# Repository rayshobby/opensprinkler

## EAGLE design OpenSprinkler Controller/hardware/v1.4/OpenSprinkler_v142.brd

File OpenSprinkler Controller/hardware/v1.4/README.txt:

OpenSprinkler v1.42 (minor update)
Changes from v1.4

- Added one 5.6V zener diode and removed the PTC fuse.
- Changed capacitor CT to 100pF in order to reduce switching regulator noise.
- Combined four 10K resistors from 1.4u to one 10Kx4resistor network.
- Switching positions of rain sensor terminal and zone expansion connector. Expansion connector now uses 2×4 right-angle male header.

=================================

OpenSprinkler v1.4 (minor update)
Changes from v1.3:

- Added DS1307 real-time clock (RTC) and button cell battery (CR1220). Removed 24LC128 external EEPROM due to PCB space constraint.
- Changed a couple of pin connections for the shift register and LCD. D3 is now used for rain sensor (can be used for other purpose if not using a rain sensor). Analog pins A2 and A3 are free; also, if not using RFM12B transceiver, digital pins D2 and D10 are free.
- Added SMT (surface mount) version 1.4s. The SMT version has two additional analog pins A6 and A7 due to the surface mount version of ATmega328. The RJ45 Ethernet jack is changed to use HanRun H911105A.

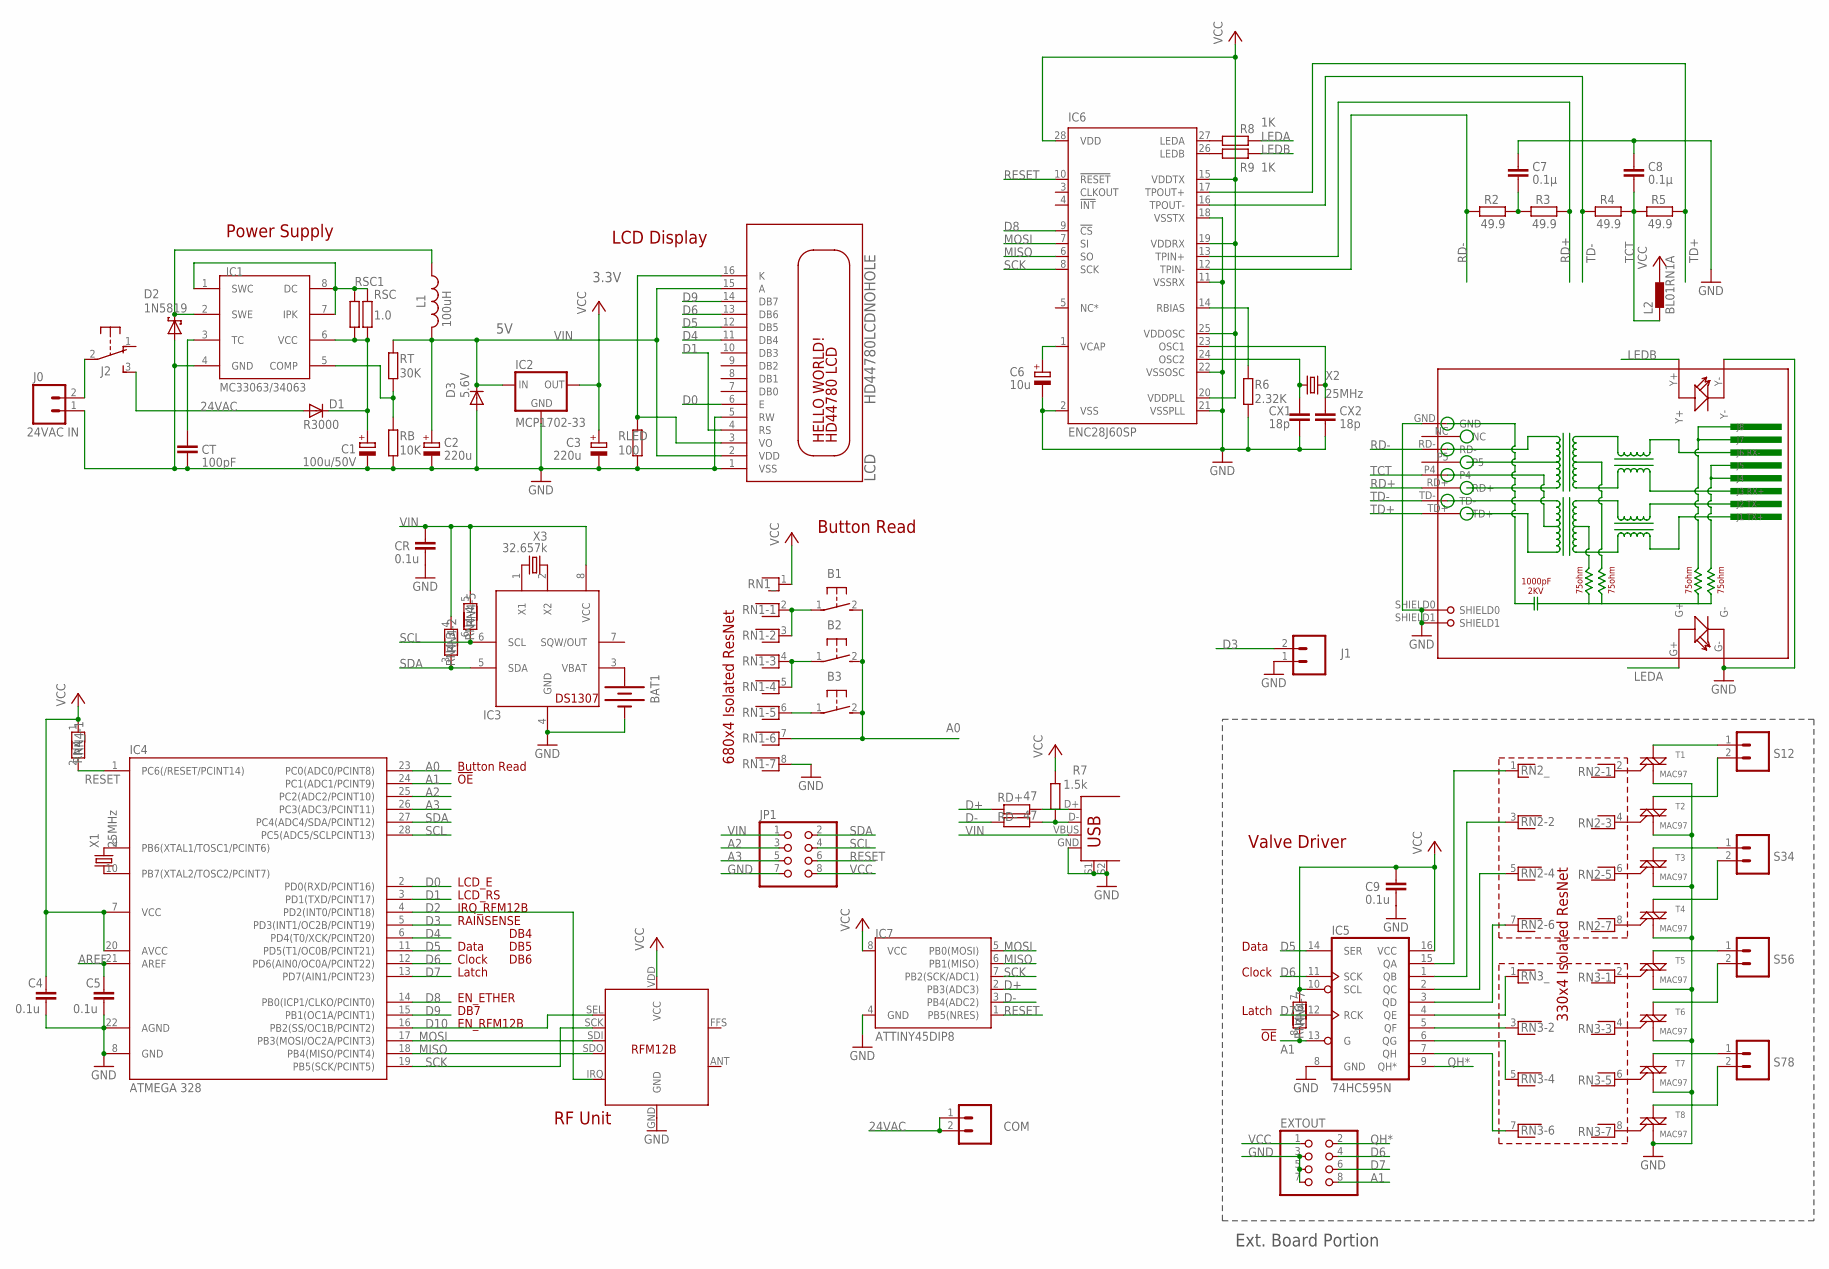
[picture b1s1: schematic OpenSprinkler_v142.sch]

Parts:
B1, B2, B3: 31-XX; B3F-31XX
BAT1: BATTERY12PTH; BATTCON_12MM_PTH
C1: 100u/50V; E3,5-8
C2, C3: 220u; E2-5
C4, C5, C9: 0.1u; C025-024X044
C6: 10u; E1,8-4
C7, C8: 0.1µ; C025-024X044
COM: M025MM; SCREWTERMINAL-5MM-2
CR: 0.1u; C025-024X044
CT: 100pF; C025-024X044
CX1, CX2: 18p; C025-024X044
D1: R3000; DO41-7.6
D2: 1N5819; DO41-7.6
D3: 5.6V; DO35-7
EXTOUT: PINHD-2X4; 2X04
IC1: MC33063/MC34063P; DIL08
IC2: MCP1702-33; TO92-INLINE
IC3: DS1307; DIL08
IC4: ATMEGA 328; DIL28-3
IC5: 74HC595N; DIL16
IC6: ENC28J60SP; DIL28-3
IC7: ATTINY45DIP8; DIP08
IC8: RFM12B
J0: 24VAC IN; SCREWTERMINAL-5MM-2
J1: M025MM; SCREWTERMINAL-5MM-2
J2: EG1206
JP1: PINHD-2X4; 2X04
L1: 100uH; 6000-XXXX-RC
L2: BL01RN1A
LCD: HD44780LCDNOHOLE; LCD1602A
R2, R3, R4, R5: 49.9; 0204/7
R6: 2.32K; 0204/7
R7: 1.5k; 0204/7
R8, R9: 1K; 0204/7
RB: 10K; 0204/7
RD+: 47; 0204/7
RD-: 47; 0204/7
RJ1: HR911105A
RLED: 100; 0204/7
RN1, RN2, RN3, RN4: RNX7; RN-8
RSC, RSC1: 1.0; 0204/7
RT: 30K; 0204/7
S12, S34, S56, S78: M025MM; SCREWTERMINAL-5MM-2
T1, T2, T3, T4, T5, T6, T7, T8: MAC97; TO-92
USB: USB+SHIELD; USB-B-PTH
X1, X2: 25MHz; HC49US
X3: 32.657k; TC26H

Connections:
24VAC: COM.1, COM.2, D1.A, J2.3 (S)
A0: B1.2 (S), B2.2 (S), B3.2 (S), IC4.23 (PC0(ADC0/PCINT8)), RN1.7
A1: EXTOUT.8, IC4.24 (PC1(ADC1/PCINT9)), IC5.13 (G), RN4.8
A2: IC4.25 (PC2(ADC2/PCINT10)), JP1.3
A3: IC4.26 (PC3(ADC3/PCINT11)), JP1.5
AREF: C5.1, IC4.21 (AREF)
D0: IC4.2 (PD0(RXD/PCINT16)), LCD.6 (E)
D1: IC4.3 (PD1(TXD/PCINT17)), LCD.4 (RS)
D2: IC4.4 (PD2(INT0/PCINT18)), IC8.IRQ
D3: IC4.5 (PD3(INT1/OC2B/PCINT19)), J1.2
D4: IC4.6 (PD4(T0/XCK/PCINT20)), LCD.11 (DB4)
D5: IC4.11 (PD5(T1/OC0B/PCINT21)), IC5.14 (SER), LCD.12 (DB5)
D6: EXTOUT.4, IC4.12 (PD6(AIN0/OC0A/PCINT22)), IC5.11 (SCK), LCD.13 (DB6)
D7: EXTOUT.6, IC4.13 (PD7(AIN1/PCINT23)), IC5.12 (RCK)
D8: IC4.14 (PB0(ICP1/CLKO/PCINT0)), IC6.9 (!CS)
D9: IC4.15 (PB1(OC1A/PCINT1)), LCD.14 (DB7)
D10: IC4.16 (PB2(SS/OC1B/PCINT2)), IC8.SEL
D+: IC7.2 (PB3(ADC3)), RD+.1
D-: IC7.3 (PB4(ADC2)), RD-.1
GND: BAT1.GND (-), C1.-, C2.-, C3.-, C4.2, C5.2, C6.-, C7.1, C8.1, C9.2, CR.2, CT.2, CX1.2, CX2.2, D2.A, D3.A, EXTOUT.3, EXTOUT.5, EXTOUT.7, IC1.4 (GND), IC2.1 (GND), IC3.4 (GND), IC4.8 (GND), IC4.22 (AGND), IC5.8 (GND), IC6.2 (VSS), IC6.11 (VSSRX), IC6.18 (VSSTX), IC6.21 (VSSPLL), IC6.22 (VSSOSC), IC7.4 (GND), IC8.GND, J0.1, J1.1, JP1.7, LCD.1 (VSS), LCD.5 (RW), R6.2, RB.2, RJ1.G-, RJ1.GND, RJ1.SHIELD0, RJ1.SHIELD1, RJ1.Y-, RLED.2, RN1.8, T1.1 (M1), T2.1 (M1), T3.1 (M1), T4.1 (M1), T5.1 (M1), T6.1 (M1), T7.1 (M1), T8.1 (M1), USB.GND, USB.S1, USB.S2
LEDA: R8.2, RJ1.G+
LEDB: R9.2, RJ1.Y+
MISO: IC4.18 (PB4(MISO/PCINT4)), IC6.6 (SO), IC7.6 (PB1(MISO)), IC8.SDO
MOSI: IC4.17 (PB3(MOSI/OC2A/PCINT3)), IC6.7 (SI), IC7.5 (PB0(MOSI)), IC8.SDI
unnamed: IC4.9 (PB6(XTAL1/TOSC1/PCINT6)), X1.2
unnamed: RN2.2, T1.2 (G)
unnamed: IC5.5 (QF), RN3.3
unnamed: IC5.6 (QG), RN3.5
unnamed: J0.2, J2.2
unnamed: IC5.7 (QH), RN3.7
unnamed: IC4.10 (PB7(XTAL2/TOSC2/PCINT7)), X1.1
unnamed: C1.+, D1.C, IC1.6 (VCC), RSC.2, RSC1.2
unnamed: IC5.4 (QE), RN3.1
unnamed: IC5.3 (QD), RN2.7
unnamed: IC5.2 (QC), RN2.5
unnamed: IC5.1 (QB), RN2.3
unnamed: IC5.15 (QA), RN2.1
unnamed: RN2.4, T2.2 (G)
unnamed: S12.1, T1.3 (M2)
unnamed: S12.2, T2.3 (M2)
unnamed: S34.1, T3.3 (M2)
unnamed: RN2.6, T3.2 (G)
unnamed: S34.2, T4.3 (M2)
unnamed: RN2.8, T4.2 (G)
unnamed: S56.1, T5.3 (M2)
unnamed: S56.2, T6.3 (M2)
unnamed: S78.1, T7.3 (M2)
unnamed: S78.2, T8.3 (M2)
unnamed: RN3.2, T5.2 (G)
unnamed: RN3.4, T6.2 (G)
unnamed: RN3.6, T7.2 (G)
unnamed: RN3.8, T8.2 (G)
unnamed: B1.1, RN1.2, RN1.3
unnamed: B3.1, RN1.6
unnamed: B2.1, RN1.4, RN1.5
unnamed: BAT1.VCC@1 (+), IC3.3 (VBAT)
unnamed: IC6.27 (LEDA), R8.1
unnamed: RD+.2, USB.D+
unnamed: IC6.26 (LEDB), R9.1
unnamed: IC1.1 (SWC), IC1.7 (IPK), IC1.8 (DC), RSC.1, RSC1.1
unnamed: R7.1, RD-.2, USB.D-
unnamed: D2.C, IC1.2 (SWE), L1.1
unnamed: IC3.2 (X2), X3.2
unnamed: LCD.3 (VO), LCD.16 (K), RLED.1
unnamed: CT.1, IC1.3 (TC)
unnamed: C6.+, IC6.1 (VCAP)
unnamed: IC6.14 (RBIAS), R6.1
unnamed: CX1.1, IC6.24 (OSC2), X2.1
unnamed: CX2.1, IC6.23 (OSC1), X2.2
unnamed: C7.2, R2.2, R3.1
unnamed: IC1.5 (COMP), RB.1, RT.2
unnamed: IC3.1 (X1), X3.1
QH*: EXTOUT.2, IC5.9 (QH*)
RD+: IC6.13 (TPIN+), R3.2, RJ1.RD+
RD-: IC6.12 (TPIN-), R2.1, RJ1.RD-
RESET: IC4.1 (PC6(/RESET/PCINT14)), IC6.10 (!RESET), IC7.1 (PB5(NRES)), JP1.6, RN4.2
SCK: IC4.19 (PB5(SCK/PCINT5)), IC6.8 (SCK), IC7.7 (PB2(SCK/ADC1)), IC8.SCK
SCL: IC3.6 (SCL), IC4.28 (PC5(ADC5/SCLPCINT13)), JP1.4, RN4.6
SDA: IC3.5 (SDA), IC4.27 (PC4(ADC4/SDA/PCINT12)), JP1.2, RN4.3
TCT: C8.2, L2.1, R4.2, R5.1, RJ1.P4
TD+: IC6.17 (TPOUT+), R5.2, RJ1.TD+
TD-: IC6.16 (TPOUT-), R4.1, RJ1.TD-
VCC: C3.+, C4.1, C9.1, EXTOUT.1, IC2.3 (OUT), IC4.7 (VCC), IC4.20 (AVCC), IC5.10 (SCL), IC5.16 (VCC), IC6.15 (VDDTX), IC6.19 (VDDRX), IC6.20 (VDDPLL), IC6.25 (VDDOSC), IC6.28 (VDD), IC7.8 (VCC), IC8.VDD (VCC), JP1.8, L2.2, R7.2, RN1.1, RN4.1, RN4.7
VIN: C2.+, CR.1, D3.C, IC2.2 (IN), IC3.8 (VCC), JP1.1, L1.2, LCD.2 (VDD), LCD.15 (A), RN4.4, RN4.5, RT.1, USB.VBUS

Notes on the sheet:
Power Supply
Button Read
Valve Driver
Data
Clock
Latch
DB4
680x4 Isolated ResNet
330x4 Isolated ResNet
LCD Display
RF Unit
IRQ_RFM12B
EN_RFM12B
EN_ETHER
3.3V
DB7
LCD_E
LCD_RS
DB6
DB5
Ext. Board Portion
!OE
RAINSENSE

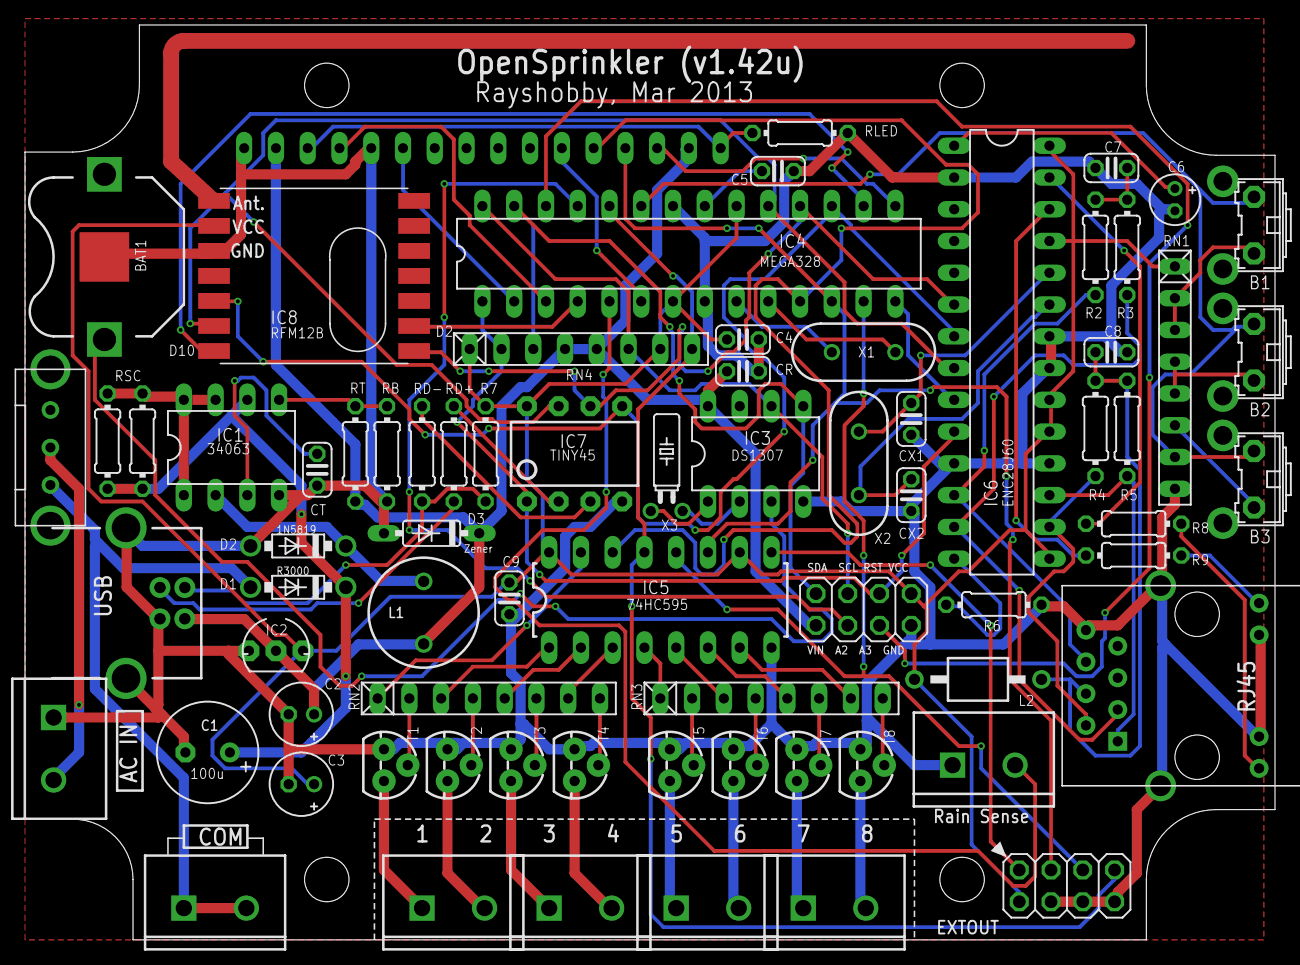
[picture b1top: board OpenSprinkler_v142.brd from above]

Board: 2 copper layers, 99.9 x 73.2 mm, 73 parts (0 on the bottom side), 84 nets.

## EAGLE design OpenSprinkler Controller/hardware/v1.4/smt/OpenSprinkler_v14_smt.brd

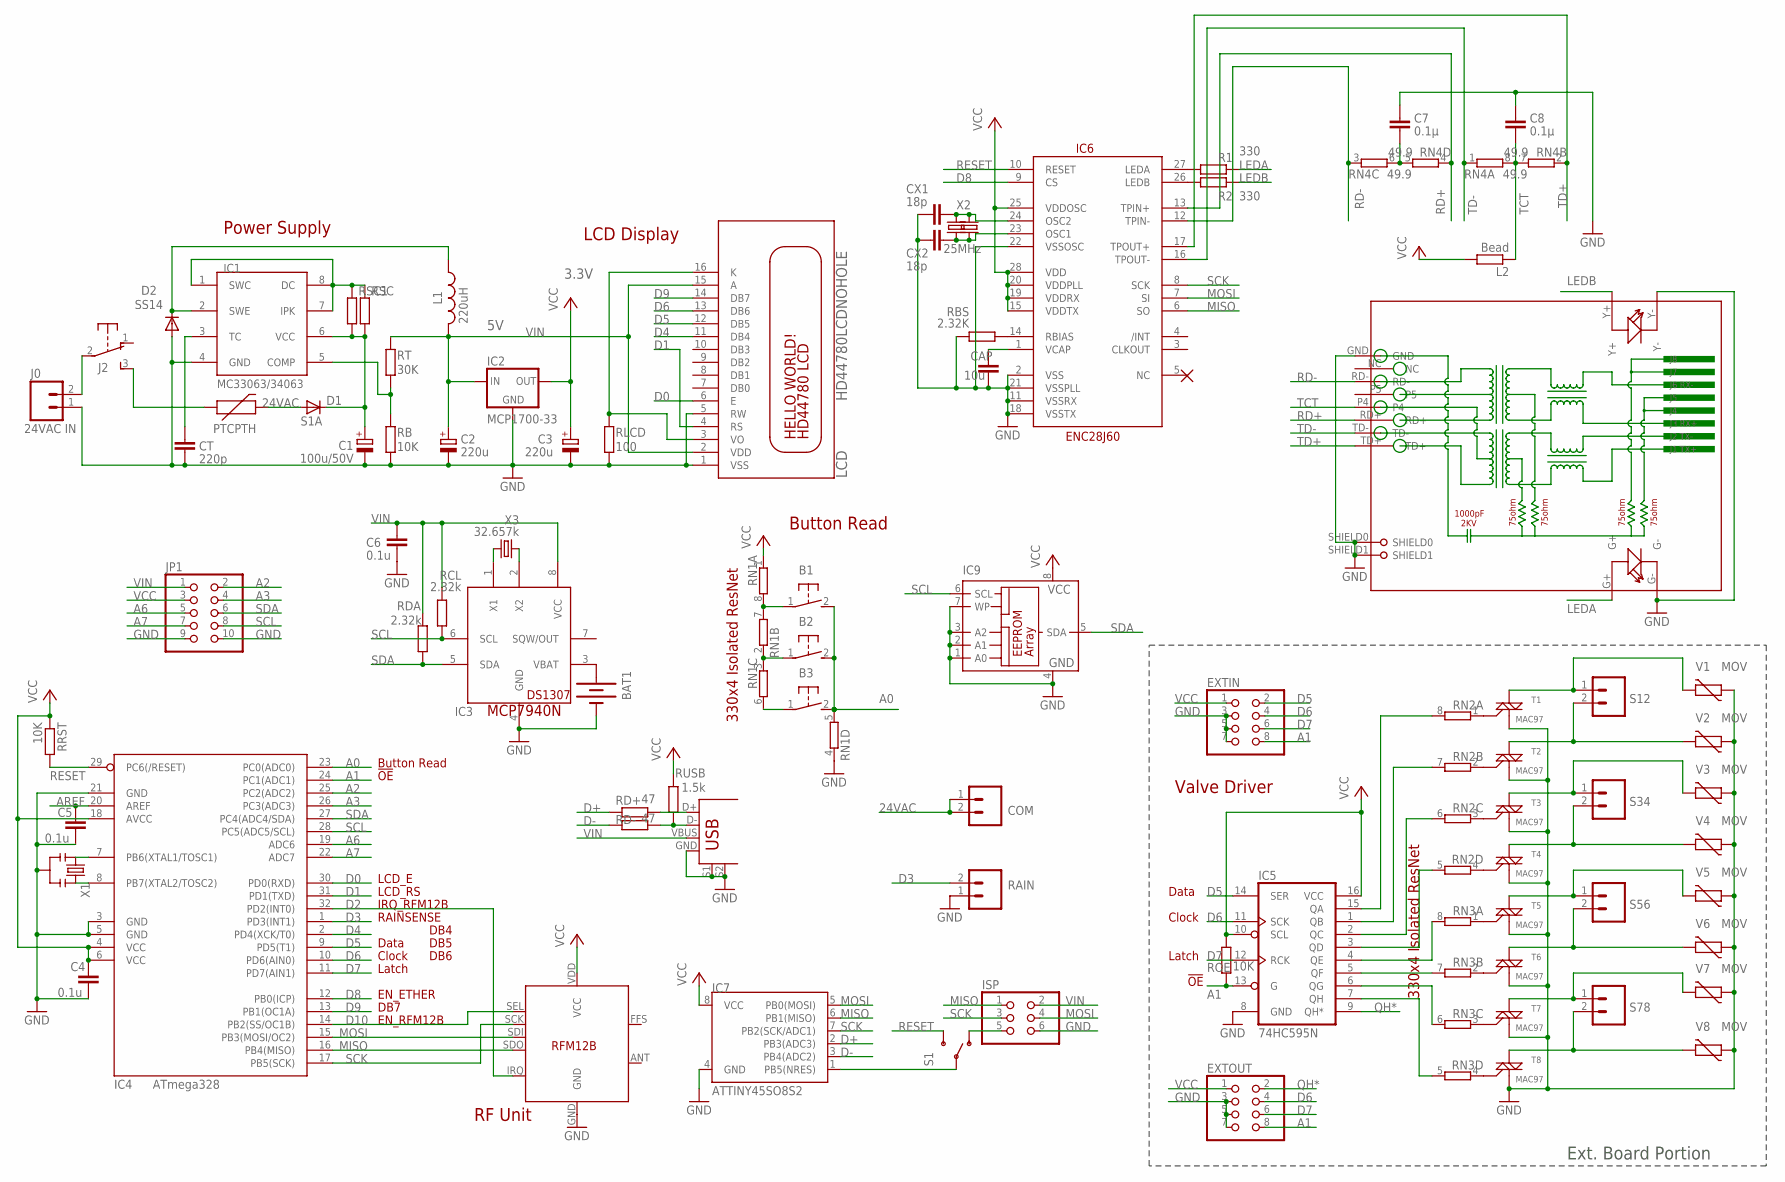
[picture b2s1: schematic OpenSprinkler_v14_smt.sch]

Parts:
B1, B2, B3: 31-XX; B3F-31XX
BAT1: BATTERY12PTH; BATTCON_12MM_PTH
C1: 100u/50V; E3,5-8
C2, C3: 220u; E2-5
C4, C5, C6: 0.1u; C0805
C7, C8: 0.1µ; C0805
CAP: 10u; C0805
COM: M025MM; SCREWTERMINAL-5MM-2
CT: 220p; C0805
CX1, CX2: 18p; C0805
D1: S1A; DO214AC
D2: SS14; DO214AC
EXTIN: PINHD-2X4; 2X04
EXTOUT: PINHD-2X4; 2X04
IC1: MC33063/MC34063D; SO08
IC2: MCP1700-33; SOT23
IC3: MCP7940N; SO08
IC4: ATmega328; TQFP32-08
IC5: 74HC595N; SO16
IC6: ENC28J60; SOIC28WLONG
IC7: ATTINY45SO8S2; SO8S2
IC8: RFM12B
IC9: 24AA128SN; SO-08
ISP: PINHD-2X3; 2X03
J0: 24VAC IN; SCREWTERMINAL-5MM-2
J2: EG1206
JP1: PINHD-2X5; 2X05
L1: 220uH; 6000-XXXX-RC
L2: Bead; R0805
LCD: HD44780LCDNOHOLE; LCD1602A
PTC: PTCPTH; PTC
R1, R2: 330; R0805
RAIN: M025MM; SCREWTERMINAL-5MM-2
RB: 10K; R0805
RBS: 2.32K; R0805
RCL: 2.32k; R0805
RD+: 47; R0805
RD-: 47; R0805
RDA: 2.32k; R0805
RJ1: HR911105A
RLCD: 100; R0805
RN1, RN2, RN3: 4R-NEXBV8V; EXBV8V
RN4: 49.9; EXBV8V
ROE: 10K; R0805
RRST: 10K; R0805
RSC, RSC1: 1.0; R0805
RT: 30K; R0805
RUSB: 1.5k; R0805
S1: SWITCH-SPSTSMD2; SWITCH-SPDT-SMD
S12, S34, S56, S78: M025MM; SCREWTERMINAL-5MM-2
T1, T2, T3, T4, T5, T6, T7, T8: MAC97; SOT223
USB: USB+SHIELD; USB-B-PTH
V1, V2, V3, V4, V5, V6, V7, V8: MOV; R-5
X1: RESONATORSMD; RESONATOR-SMD
X2: 25MHz; HC49UP
X2A: 25MHz; HC49US
X3: 32.657k; TC26H

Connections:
24VAC: COM.1, COM.2, D1.A, PTC.P$2 (2)
A0: B1.2 (S), B2.2 (S), B3.2 (S), IC4.23 (PC0(ADC0)), RN1.5 (2)
A1: EXTIN.8, EXTOUT.8, IC4.24 (PC1(ADC1)), IC5.13 (G), ROE.1
A2: IC4.25 (PC2(ADC2)), JP1.2
A3: IC4.26 (PC3(ADC3)), JP1.4
A6: IC4.19 (ADC6), JP1.5
A7: IC4.22 (ADC7), JP1.7
AREF: C5.1, IC4.20 (AREF)
D0: IC4.30 (PD0(RXD)), LCD.6 (E)
D1: IC4.31 (PD1(TXD)), LCD.4 (RS)
D2: IC4.32 (PD2(INT0)), IC8.IRQ
D3: IC4.1 (PD3(INT1)), RAIN.2
D4: IC4.2 (PD4(XCK/T0)), LCD.11 (DB4)
D5: EXTIN.2, IC4.9 (PD5(T1)), IC5.14 (SER), LCD.12 (DB5)
D6: EXTIN.4, EXTOUT.4, IC4.10 (PD6(AIN0)), IC5.11 (SCK), LCD.13 (DB6)
D7: EXTIN.6, EXTOUT.6, IC4.11 (PD7(AIN1)), IC5.12 (RCK)
D8: IC4.12 (PB0(ICP)), IC6.9 (CS)
D9: IC4.13 (PB1(OC1A)), LCD.14 (DB7)
D10: IC4.14 (PB2(SS/OC1B)), IC8.SEL
D+: IC7.2 (PB3(ADC3)), RD+.1
D-: IC7.3 (PB4(ADC2)), RD-.1
GND: BAT1.GND (-), C1.-, C2.-, C3.-, C4.2, C5.2, C6.2, C7.1, C8.1, CAP.2, CT.2, CX1.2, CX2.2, D2.A, EXTIN.3, EXTIN.5, EXTIN.7, EXTOUT.3, EXTOUT.5, EXTOUT.7, IC1.4 (GND), IC2.1 (GND), IC3.4 (GND), IC4.3 (GND), IC4.5 (GND), IC4.21 (GND), IC5.8 (GND), IC6.2 (VSS), IC6.11 (VSSRX), IC6.18 (VSSTX), IC6.21 (VSSPLL), IC6.22 (VSSOSC), IC7.4 (GND), IC8.GND, IC9.1 (A0), IC9.2 (A1), IC9.3 (A2), IC9.4 (GND), IC9.7 (WP), ISP.6, J0.1, JP1.9, JP1.10, LCD.1 (VSS), LCD.5 (RW), RAIN.1, RB.2, RBS.1, RJ1.G-, RJ1.GND, RJ1.SHIELD0, RJ1.SHIELD1, RJ1.Y-, RLCD.2, RN1.4 (1), T1.1 (M1), T2.1 (M1), T3.1 (M1), T4.1 (M1), T5.1 (M1), T6.1 (M1), T7.1 (M1), T8.1 (M1), USB.GND, USB.S1, USB.S2, V1.1, V2.1, V3.1, V4.1, V5.1, V6.1, V7.1, V8.1, X1.2
LEDA: R1.2, RJ1.G+
LEDB: R2.2, RJ1.Y+
MISO: IC4.16 (PB4(MISO)), IC6.6 (SO), IC7.6 (PB1(MISO)), IC8.SDO, ISP.1
MOSI: IC4.15 (PB3(MOSI/OC2)), IC6.7 (SI), IC7.5 (PB0(MOSI)), IC8.SDI, ISP.4
unnamed: IC4.8 (PB7(XTAL2/TOSC2)), X1.3
unnamed: RN2.1, T1.3 (G)
unnamed: IC5.5 (QF), RN3.7 (2)
unnamed: IC5.6 (QG), RN3.6 (2)
unnamed: J0.2, J2.2
unnamed: IC5.7 (QH), RN3.5 (2)
unnamed: IC4.7 (PB6(XTAL1/TOSC1)), X1.1
unnamed: C1.+, D1.C, IC1.6 (VCC), RSC.2, RSC1.2
unnamed: IC5.4 (QE), RN3.8 (2)
unnamed: IC5.3 (QD), RN2.5 (2)
unnamed: IC5.2 (QC), RN2.6 (2)
unnamed: IC5.1 (QB), RN2.7 (2)
unnamed: IC5.15 (QA), RN2.8 (2)
unnamed: RN2.2 (1), T2.3 (G)
unnamed: S12.1, T1.4 (M2), V1.2
unnamed: S12.2, T2.4 (M2), V2.2
unnamed: S34.1, T3.4 (M2), V3.2
unnamed: RN2.3 (1), T3.3 (G)
unnamed: S34.2, T4.4 (M2), V4.2
unnamed: RN2.4 (1), T4.3 (G)
unnamed: S56.1, T5.4 (M2), V5.2
unnamed: S56.2, T6.4 (M2), V6.2
unnamed: S78.1, T7.4 (M2), V7.2
unnamed: S78.2, T8.4 (M2), V8.2
unnamed: RN3.1, T5.3 (G)
unnamed: RN3.2 (1), T6.3 (G)
unnamed: RN3.3 (1), T7.3 (G)
unnamed: RN3.4 (1), T8.3 (G)
unnamed: ISP.5, S1.1 (O)
unnamed: J2.3 (S), PTC.P$1 (1)
unnamed: B1.1, RN1.7 (2), RN1.8 (2)
unnamed: B3.1, RN1.6 (2)
unnamed: IC6.27 (LEDA), R1.1
unnamed: B2.1, RN1.2 (1), RN1.3 (1)
unnamed: BAT1.VCC@1 (+), IC3.3 (VBAT)
unnamed: IC6.26 (LEDB), R2.1
unnamed: RD+.2, USB.D+
unnamed: CAP.1, IC6.1 (VCAP)
unnamed: IC1.1 (SWC), IC1.7 (IPK), IC1.8 (DC), RSC.1, RSC1.1
unnamed: CX1.1, IC6.24 (OSC2), X2.1, X2A.2
unnamed: CX2.1, IC6.23 (OSC1), X2.2, X2A.1
unnamed: RD-.2, RUSB.1, USB.D-
unnamed: D2.C, IC1.2 (SWE), L1.1
unnamed: IC3.1 (X1), X3.1
unnamed: CT.1, IC1.3 (TC)
unnamed: IC3.2 (X2), X3.2
unnamed: IC7.1 (PB5(NRES)), S1.2
unnamed: C7.2, RN4.5 (2), RN4.6 (2)
unnamed: IC1.5 (COMP), RB.1, RT.2
unnamed: LCD.3 (VO), LCD.16 (K), RLCD.1
unnamed: IC6.14 (RBIAS), RBS.2
QH*: EXTOUT.2, IC5.9 (QH*)
RD+: IC6.13 (TPIN+), RJ1.RD+, RN4.4 (1)
RD-: IC6.12 (TPIN-), RJ1.RD-, RN4.3 (1)
RESET: IC4.29 (PC6(/RESET)), IC6.10 (RESET), RRST.2, S1.3 (S)
SCK: IC4.17 (PB5(SCK)), IC6.8 (SCK), IC7.7 (PB2(SCK/ADC1)), IC8.SCK, ISP.3
SCL: IC3.6 (SCL), IC4.28 (PC5(ADC5/SCL)), IC9.6 (SCL), JP1.8, RCL.2
SDA: IC3.5 (SDA), IC4.27 (PC4(ADC4/SDA)), IC9.5 (SDA), JP1.6, RDA.2
TCT: C8.2, L2.1, RJ1.P4, RN4.7 (2), RN4.8 (2)
TD+: IC6.17 (TPOUT+), RJ1.TD+, RN4.2 (1)
TD-: IC6.16 (TPOUT-), RJ1.TD-, RN4.1
VCC: C3.+, C4.1, EXTIN.1, EXTOUT.1, IC2.2 (OUT), IC4.4 (VCC), IC4.6 (VCC), IC4.18 (AVCC), IC5.10 (SCL), IC5.16 (VCC), IC6.15 (VDDTX), IC6.19 (VDDRX), IC6.20 (VDDPLL), IC6.25 (VDDOSC), IC6.28 (VDD), IC7.8 (VCC), IC8.VDD (VCC), IC9.8 (VCC), JP1.3, L2.2, RN1.1, ROE.2, RRST.1, RUSB.2
VIN: C2.+, C6.1, IC2.3 (IN), IC3.8 (VCC), ISP.2, JP1.1, L1.2, LCD.2 (VDD), LCD.15 (A), RCL.1, RDA.1, RT.1, USB.VBUS

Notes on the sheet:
Power Supply
Button Read
Valve Driver
Data
Clock
Latch
DB4
330x4 Isolated ResNet
LCD Display
RF Unit
IRQ_RFM12B
EN_RFM12B
EN_ETHER
3.3V
DB7
LCD_E
LCD_RS
DB6
DB5
Ext. Board Portion
!OE
RAINSENSE
MCP7940N

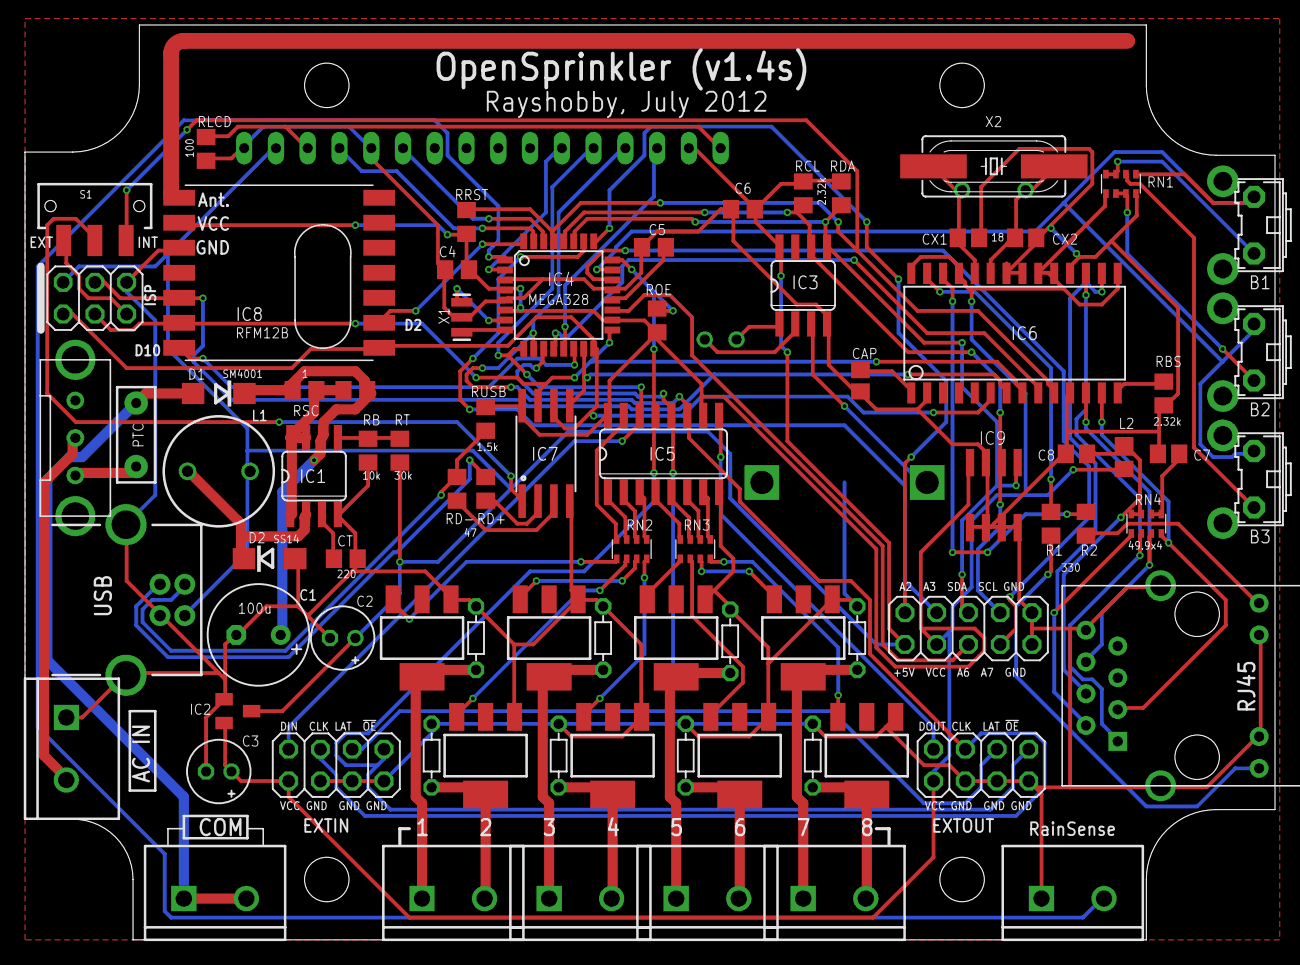
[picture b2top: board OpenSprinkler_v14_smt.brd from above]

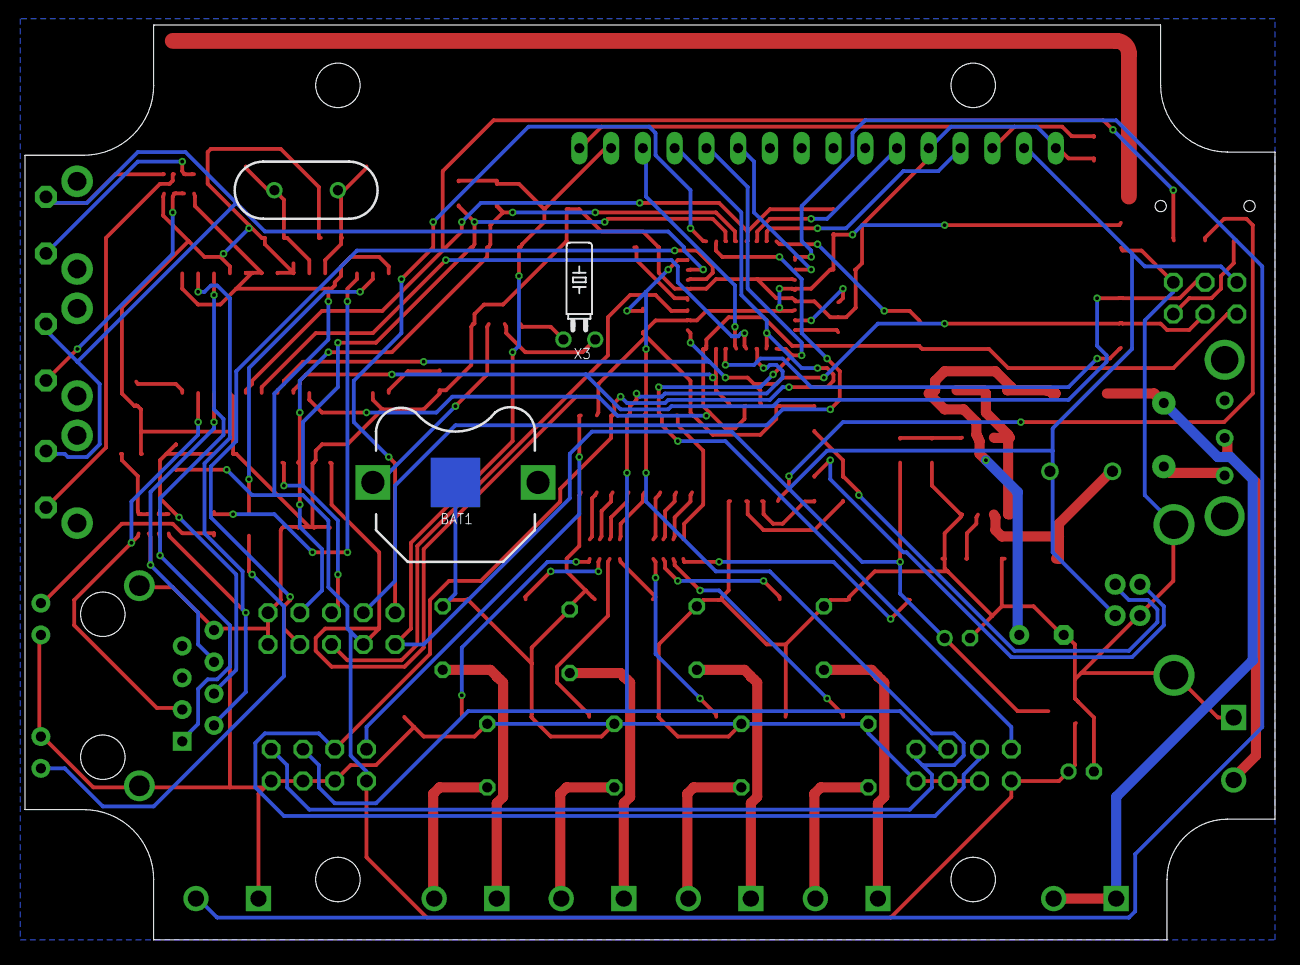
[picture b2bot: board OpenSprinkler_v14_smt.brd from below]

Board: 2 copper layers, 99.9 x 73.2 mm, 85 parts (3 on the bottom side), 89 nets.

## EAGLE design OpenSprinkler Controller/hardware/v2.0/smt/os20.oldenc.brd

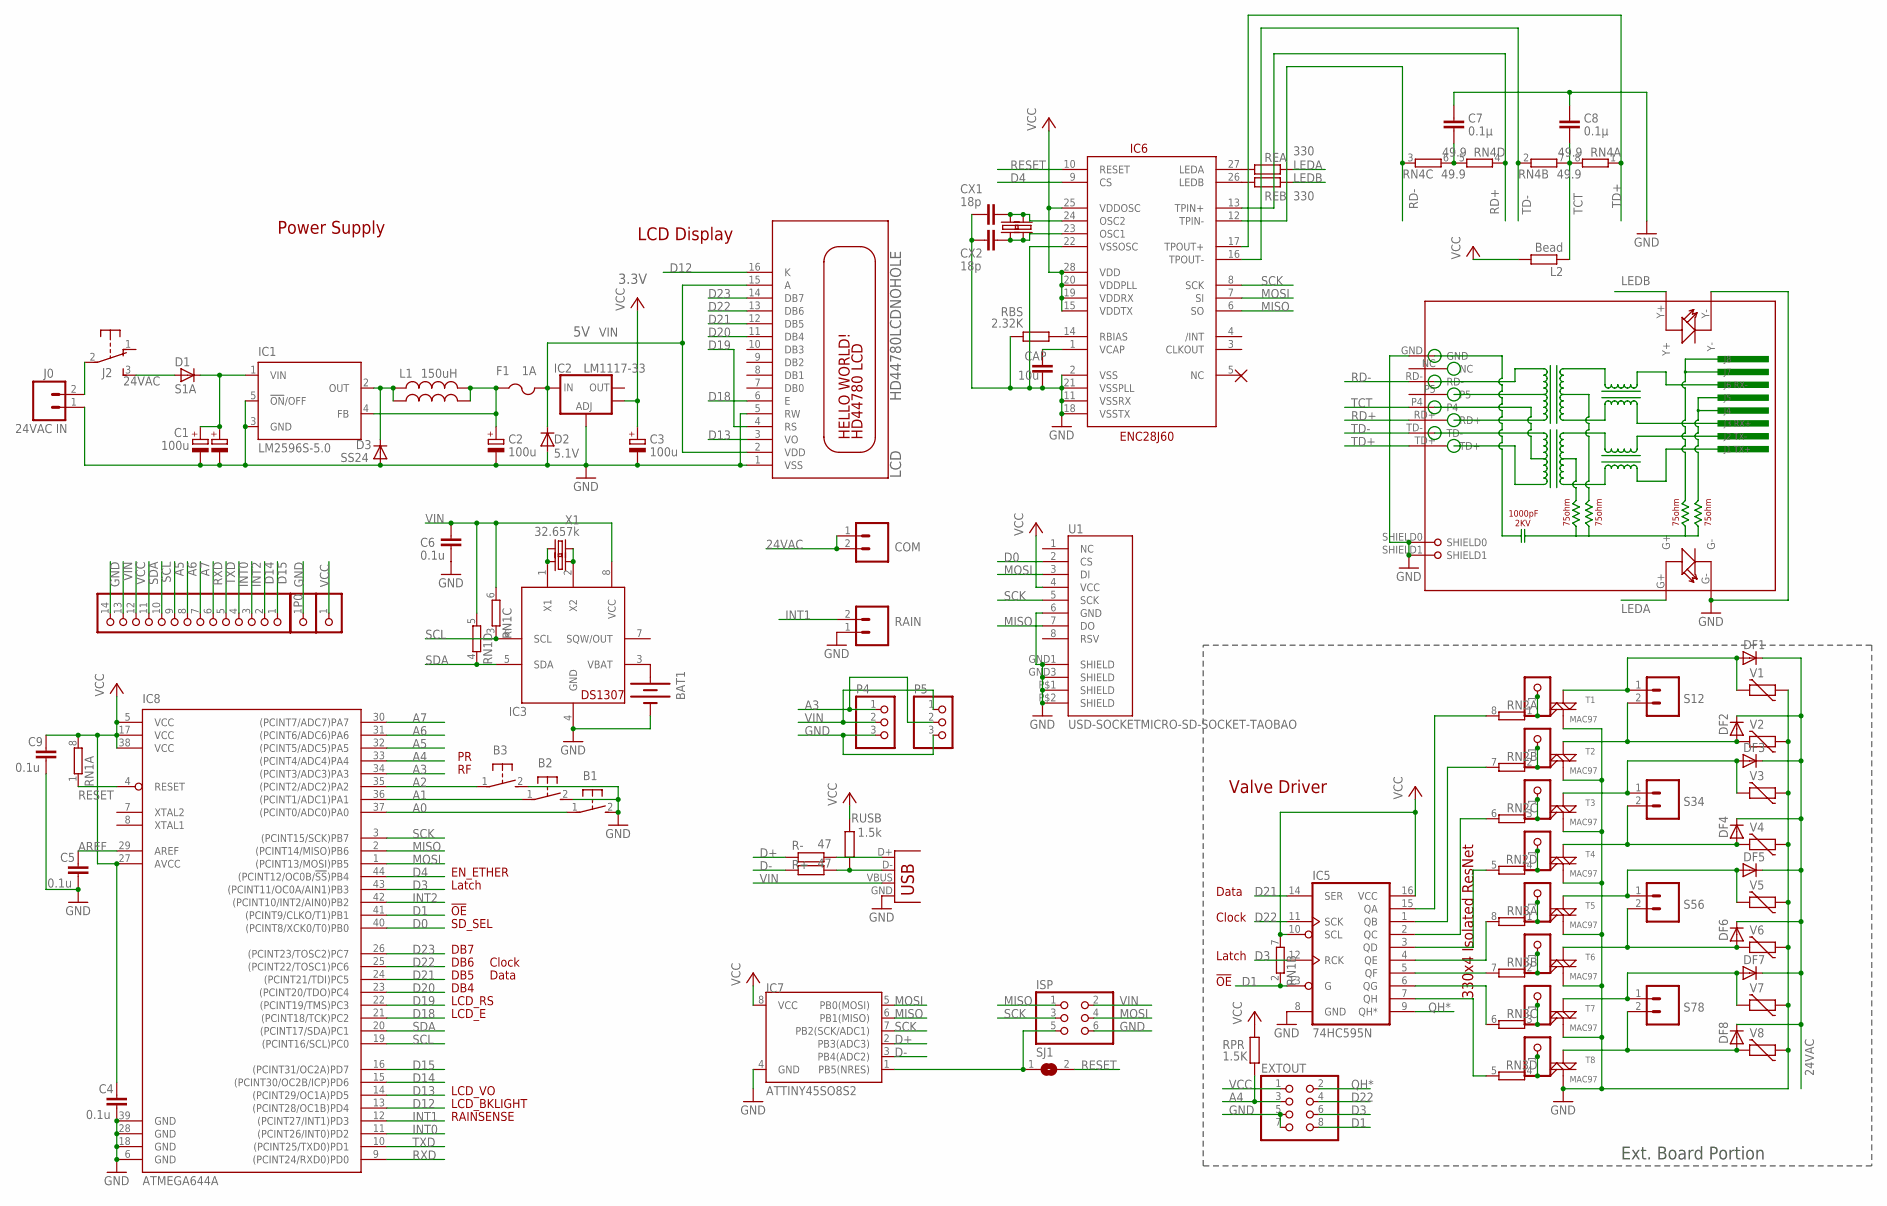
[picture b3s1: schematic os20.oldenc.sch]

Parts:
B1, B2, B3: 31-XX; B3F-31XX
BAT1: BATTERYBATTERY_12MM_SMT; BATTCON_12MM_SMT
C1: 100u; E3,5-8
C1': 100u; PANASONIC_E
C2, C3: 100u; PANASONIC_D
C4, C5, C6, C9: 0.1u; C0805
C7, C8: 0.1µ; C0805
CAP: 10u; C0805
COM: M025MM; SCREWTERMINAL-5MM-2
CX1, CX2: 18p; C0805
D1: S1A; DO-214AC
D2: 5.1V; MINIMELF
D3: SS24; DO-214AC
DF1, DF2, DF3, DF4, DF5, DF6, DF7, DF8: DIODE-D-2.5; D-2.5
EXTOUT: PINHD-2X4; 2X04
F1: 1A; 1812
IC1: LM2596S-5.0; TO263-5
IC2: LM1117-33; SOT223
IC3: DS1307; SO08
IC5: 74HC595N; SO16
IC6: ENC28J60; SOIC28WLONG
IC7: ATTINY45SO8S2; SO8S2
IC8: ATMEGA644A; TQFP44
ISP: PINHD-2X3; 2X03
J0: 24VAC IN; SCREWTERMINAL-5MM-2
J2: EG1206
JP2, JP3, JP4, JP5, JP6, JP7, JP8, JP9: PINHD-1X1CB; 1X01-CLEANBIG
L1: 150uH; 6000-XXXX-RC
L1': 220uH; CDRH125
L2: Bead; R0805
LCD: HD44780LCDNOHOLE; LCD1602A
P0: PINHD-1X14-CB; 1X14-CB
P1, P2: PINHD-1X1CB; 1X01-CLEANBIG
P4, P5: PINHD-1X3; 1X03
R+: 47; R0805
R-: 47; R0805
RAIN: M025MM; SCREWTERMINAL-5MM-2
RBS: 2.32K; R0805
REA: 330; R0805
REB: 330; R0805
RJ1: HR911105A
RN1, RN2, RN3: 4R-NEXB38V; EXB38V
RN4: 49.9; EXB38V
RPR: 1.5K; R0805
RUSB: 1.5k; R0805
S12, S34, S56, S78: M025MM; SCREWTERMINAL-5MM-2
SJ1: SJ
T1, T2, T3, T4, T5, T6, T7, T8: MAC97; SOT223
U1: USD-SOCKETMICRO-SD-SOCKET-TAOBAO; MICRO-SD-SOCKET-TAOBAO
USB: USBPTH; USB-B-PTH
V1, V2, V3, V4, V5, V6, V7, V8: MOV; R-5
X1: 32.657k; TC26H
X1'1: 32.657k; MM20SS
X2: 25MHz; CRYSTAL-SMD-10.5X4.8-2PIN
X2': 25MHz; HC49US

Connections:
24VAC: COM.1, COM.2, D1.A, DF1.C, DF2.C, DF3.C, DF4.C, DF5.C, DF6.C, DF7.C, DF8.C, J2.3 (S)
A0: B1.1, IC8.37 ((PCINT0/ADC0)PA0)
A1: B2.1, IC8.36 ((PCINT1/ADC1)PA1)
A2: B3.1, IC8.35 ((PCINT2/ADC2)PA2)
A3: IC8.34 ((PCINT3/ADC3)PA3), P4.1, P5.2
A4: EXTOUT.3, IC8.33 ((PCINT4/ADC4)PA4), RPR.1
A5: IC8.32 ((PCINT5/ADC5)PA5), P0.9
A6: IC8.31 ((PCINT6/ADC6)PA6), P0.8
A7: IC8.30 ((PCINT7/ADC7)PA7), P0.7
AREF: C5.1, IC8.29 (AREF)
D0: IC8.40 ((PCINT8/XCK0/T0)PB0), U1.2 (CS)
D1: EXTOUT.8, IC5.13 (G), IC8.41 ((PCINT9/CLKO/T1)PB1), RN1.2 (1)
D3: EXTOUT.6, IC5.12 (RCK), IC8.43 ((PCINT11/OC0A/AIN1)PB3)
D4: IC6.9 (CS), IC8.44 ((PCINT12/OC0B/!SS!)PB4)
D12: IC8.13 ((PCINT28/OC1B)PD4), LCD.16 (K)
D13: IC8.14 ((PCINT29/OC1A)PD5), LCD.3 (VO)
D14: IC8.15 ((PCINT30/OC2B/ICP)PD6), P0.2
D15: IC8.16 ((PCINT31/OC2A)PD7), P0.1
D18: IC8.21 ((PCINT18/TCK)PC2), LCD.6 (E)
D19: IC8.22 ((PCINT19/TMS)PC3), LCD.4 (RS)
D20: IC8.23 ((PCINT20/TDO)PC4), LCD.11 (DB4)
D21: IC5.14 (SER), IC8.24 ((PCINT21/TDI)PC5), LCD.12 (DB5)
D22: EXTOUT.4, IC5.11 (SCK), IC8.25 ((PCINT22/TOSC1)PC6), LCD.13 (DB6)
D23: IC8.26 ((PCINT23/TOSC2)PC7), LCD.14 (DB7)
D+: IC7.2 (PB3(ADC3)), R-.1
D-: IC7.3 (PB4(ADC2)), R+.1
GND: B1.2 (S), B2.2 (S), B3.2 (S), BAT1.P$1 (-), C1.-, C1'.-, C2.-, C3.-, C4.2, C5.2, C6.2, C7.1, C8.1, C9.2, CAP.2, CX1.2, CX2.2, D2.A, D3.A, EXTOUT.5, EXTOUT.7, IC1.3 (GND), IC1.5 (!ON!/OFF), IC2.1 (ADJ), IC3.4 (GND), IC5.8 (GND), IC6.2 (VSS), IC6.11 (VSSRX), IC6.18 (VSSTX), IC6.21 (VSSPLL), IC6.22 (VSSOSC), IC7.4 (GND), IC8.6 (GND), IC8.18 (GND), IC8.28 (GND), IC8.39 (GND), ISP.6, J0.1, LCD.1 (VSS), LCD.5 (RW), P0.14, P2.1, P4.3, P5.3, RAIN.1, RBS.1, RJ1.G-, RJ1.GND, RJ1.SHIELD0, RJ1.SHIELD1, RJ1.Y-, T1.1 (M1), T2.1 (M1), T3.1 (M1), T4.1 (M1), T5.1 (M1), T6.1 (M1), T7.1 (M1), T8.1 (M1), U1.6 (GND), U1.GND1 (SHIELD), U1.GND3 (SHIELD), U1.P$1 (SHIELD), U1.P$2 (SHIELD), USB.GND, V1.1, V2.1, V3.1, V4.1, V5.1, V6.1, V7.1, V8.1
INT0: IC8.11 ((PCINT26/INT0)PD2), P0.4
INT1: IC8.12 ((PCINT27/INT1)PD3), RAIN.2
INT2: IC8.42 ((PCINT10/INT2/AIN0)PB2), P0.3
LEDA: REA.2, RJ1.G+
LEDB: REB.2, RJ1.Y+
MISO: IC6.6 (SO), IC7.6 (PB1(MISO)), IC8.2 ((PCINT14/MISO)PB6), ISP.1, U1.7 (DO)
MOSI: IC6.7 (SI), IC7.5 (PB0(MOSI)), IC8.1 ((PCINT13/MOSI)PB5), ISP.4, U1.3 (DI)
unnamed: C1.+, C1'.+, D1.C, IC1.1 (VIN)
unnamed: C2.+, F1.1, IC1.4 (FB), L1.2, L1'.2
unnamed: JP2.1, RN2.1, T1.3 (G)
unnamed: IC5.5 (QF), RN3.7 (2)
unnamed: IC5.6 (QG), RN3.6 (2)
unnamed: J0.2, J2.2
unnamed: IC5.7 (QH), RN3.5 (2)
unnamed: IC3.1 (X1), X1.2, X1'1.1
unnamed: D3.C, IC1.2 (OUT), L1.1, L1'.1
unnamed: IC5.4 (QE), RN3.8 (2)
unnamed: IC5.3 (QD), RN2.5 (2)
unnamed: IC5.2 (QC), RN2.6 (2)
unnamed: IC5.1 (QB), RN2.7 (2)
unnamed: IC5.15 (QA), RN2.8 (2)
unnamed: JP3.1, RN2.2 (1), T2.3 (G)
unnamed: DF1.A, S12.1, T1.4 (M2), V1.2
unnamed: DF2.A, S12.2, T2.4 (M2), V2.2
unnamed: DF3.A, S34.1, T3.4 (M2), V3.2
unnamed: JP4.1, RN2.3 (1), T3.3 (G)
unnamed: DF4.A, S34.2, T4.4 (M2), V4.2
unnamed: JP5.1, RN2.4 (1), T4.3 (G)
unnamed: DF5.A, S56.1, T5.4 (M2), V5.2
unnamed: DF6.A, S56.2, T6.4 (M2), V6.2
unnamed: DF7.A, S78.1, T7.4 (M2), V7.2
unnamed: DF8.A, S78.2, T8.4 (M2), V8.2
unnamed: JP6.1, RN3.1, T5.3 (G)
unnamed: JP7.1, RN3.2 (1), T6.3 (G)
unnamed: JP8.1, RN3.3 (1), T7.3 (G)
unnamed: JP9.1, RN3.4 (1), T8.3 (G)
unnamed: IC3.2 (X2), X1.1, X1'1.4 (2)
unnamed: IC6.27 (LEDA), REA.1
unnamed: BAT1.P$2 (+), IC3.3 (VBAT)
unnamed: IC6.26 (LEDB), REB.1
unnamed: R-.2, USB.D+
unnamed: CAP.1, IC6.1 (VCAP)
unnamed: CX1.1, IC6.24 (OSC2), X2.P$2 (2), X2'.2
unnamed: CX2.1, IC6.23 (OSC1), X2.P$1 (1), X2'.1
unnamed: R+.2, RUSB.1, USB.D-
unnamed: IC7.1 (PB5(NRES)), ISP.5, SJ1.1
unnamed: C7.2, RN4.5 (2), RN4.6 (2)
unnamed: IC6.14 (RBIAS), RBS.2
QH*: EXTOUT.2, IC5.9 (QH*)
RD+: IC6.13 (TPIN+), RJ1.RD+, RN4.4 (1)
RD-: IC6.12 (TPIN-), RJ1.RD-, RN4.3 (1)
RESET: IC6.10 (RESET), IC8.4 (RESET), RN1.1, SJ1.2
RXD: IC8.9 ((PCINT24/RXD0)PD0), P0.6
SCK: IC6.8 (SCK), IC7.7 (PB2(SCK/ADC1)), IC8.3 ((PCINT15/SCK)PB7), ISP.3, U1.5 (SCK)
SCL: IC3.6 (SCL), IC8.19 ((PCINT16/SCL)PC0), P0.10, RN1.3 (1)
SDA: IC3.5 (SDA), IC8.20 ((PCINT17/SDA)PC1), P0.11, RN1.4 (1)
TCT: C8.2, L2.1, RJ1.P4, RN4.7 (2), RN4.8 (2)
TD+: IC6.17 (TPOUT+), RJ1.TD+, RN4.1
TD-: IC6.16 (TPOUT-), RJ1.TD-, RN4.2 (1)
TXD: IC8.10 ((PCINT25/TXD0)PD1), P0.5
VCC: C3.+, C4.1, C9.1, EXTOUT.1, IC2.4 (OUT), IC5.10 (SCL), IC5.16 (VCC), IC6.15 (VDDTX), IC6.19 (VDDRX), IC6.20 (VDDPLL), IC6.25 (VDDOSC), IC6.28 (VDD), IC7.8 (VCC), IC8.5 (VCC), IC8.17 (VCC), IC8.27 (AVCC), IC8.38 (VCC), L2.2, P0.12, P1.1, RN1.7 (2), RN1.8 (2), RPR.2, RUSB.2, U1.4 (VCC)
VIN: C6.1, D2.C, F1.2, IC2.3 (IN), IC3.8 (VCC), ISP.2, LCD.2 (VDD), LCD.15 (A), P0.13, P4.2, P5.1, RN1.5 (2), RN1.6 (2), USB.VBUS

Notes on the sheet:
Power Supply
Valve Driver
Data
Clock
Latch
DB4
330x4 Isolated ResNet
LCD Display
EN_ETHER
3.3V
DB7
LCD_E
LCD_RS
DB6
DB5
Ext. Board Portion
!OE
RAINSENSE
LCD_BKLIGHT
LCD_VO
SD_SEL

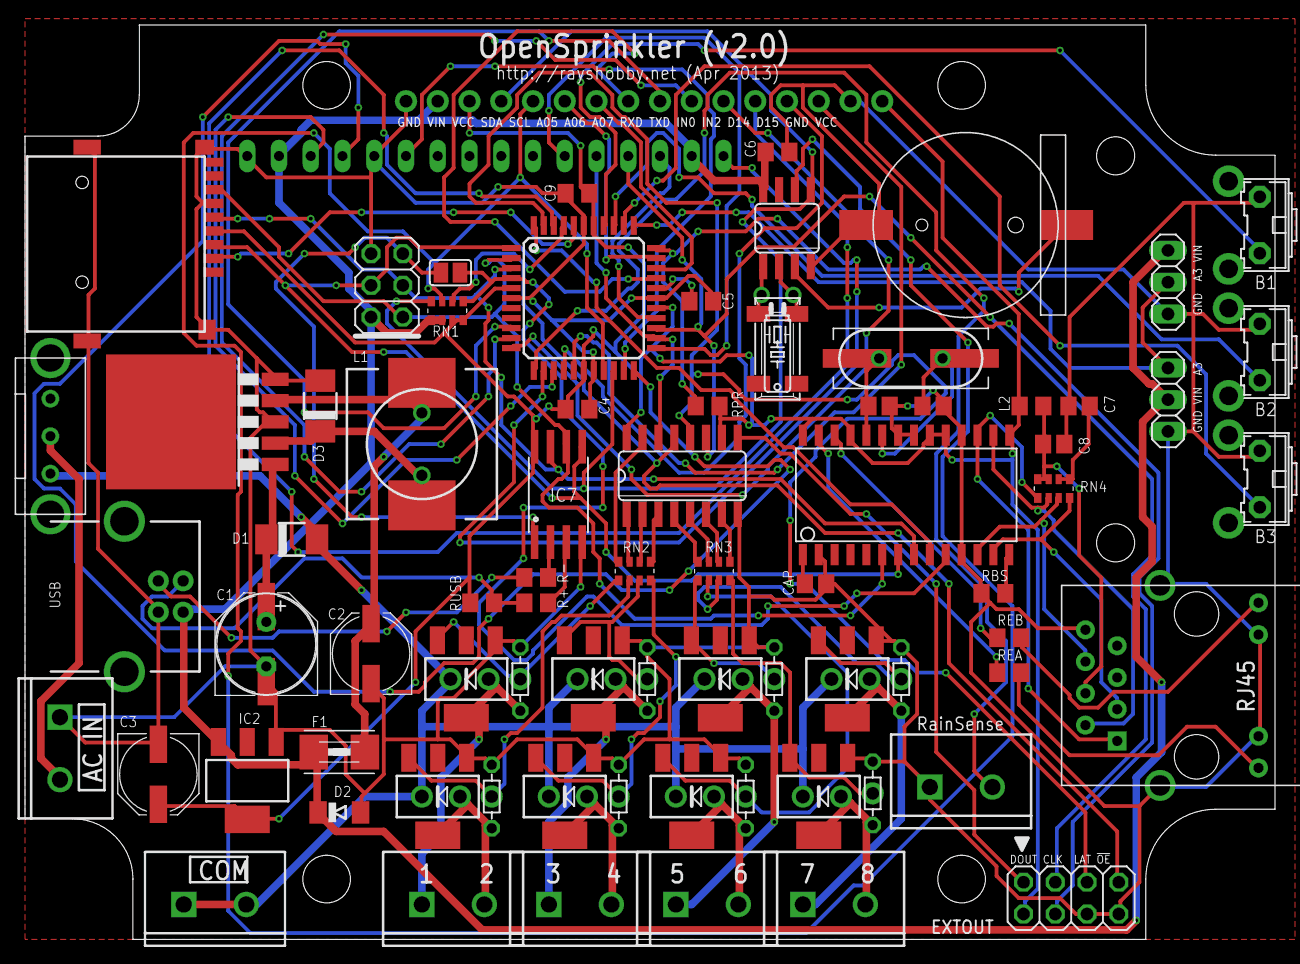
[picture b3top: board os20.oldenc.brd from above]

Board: 2 copper layers, 100.0 x 73.2 mm, 98 parts (0 on the bottom side), 89 nets.
